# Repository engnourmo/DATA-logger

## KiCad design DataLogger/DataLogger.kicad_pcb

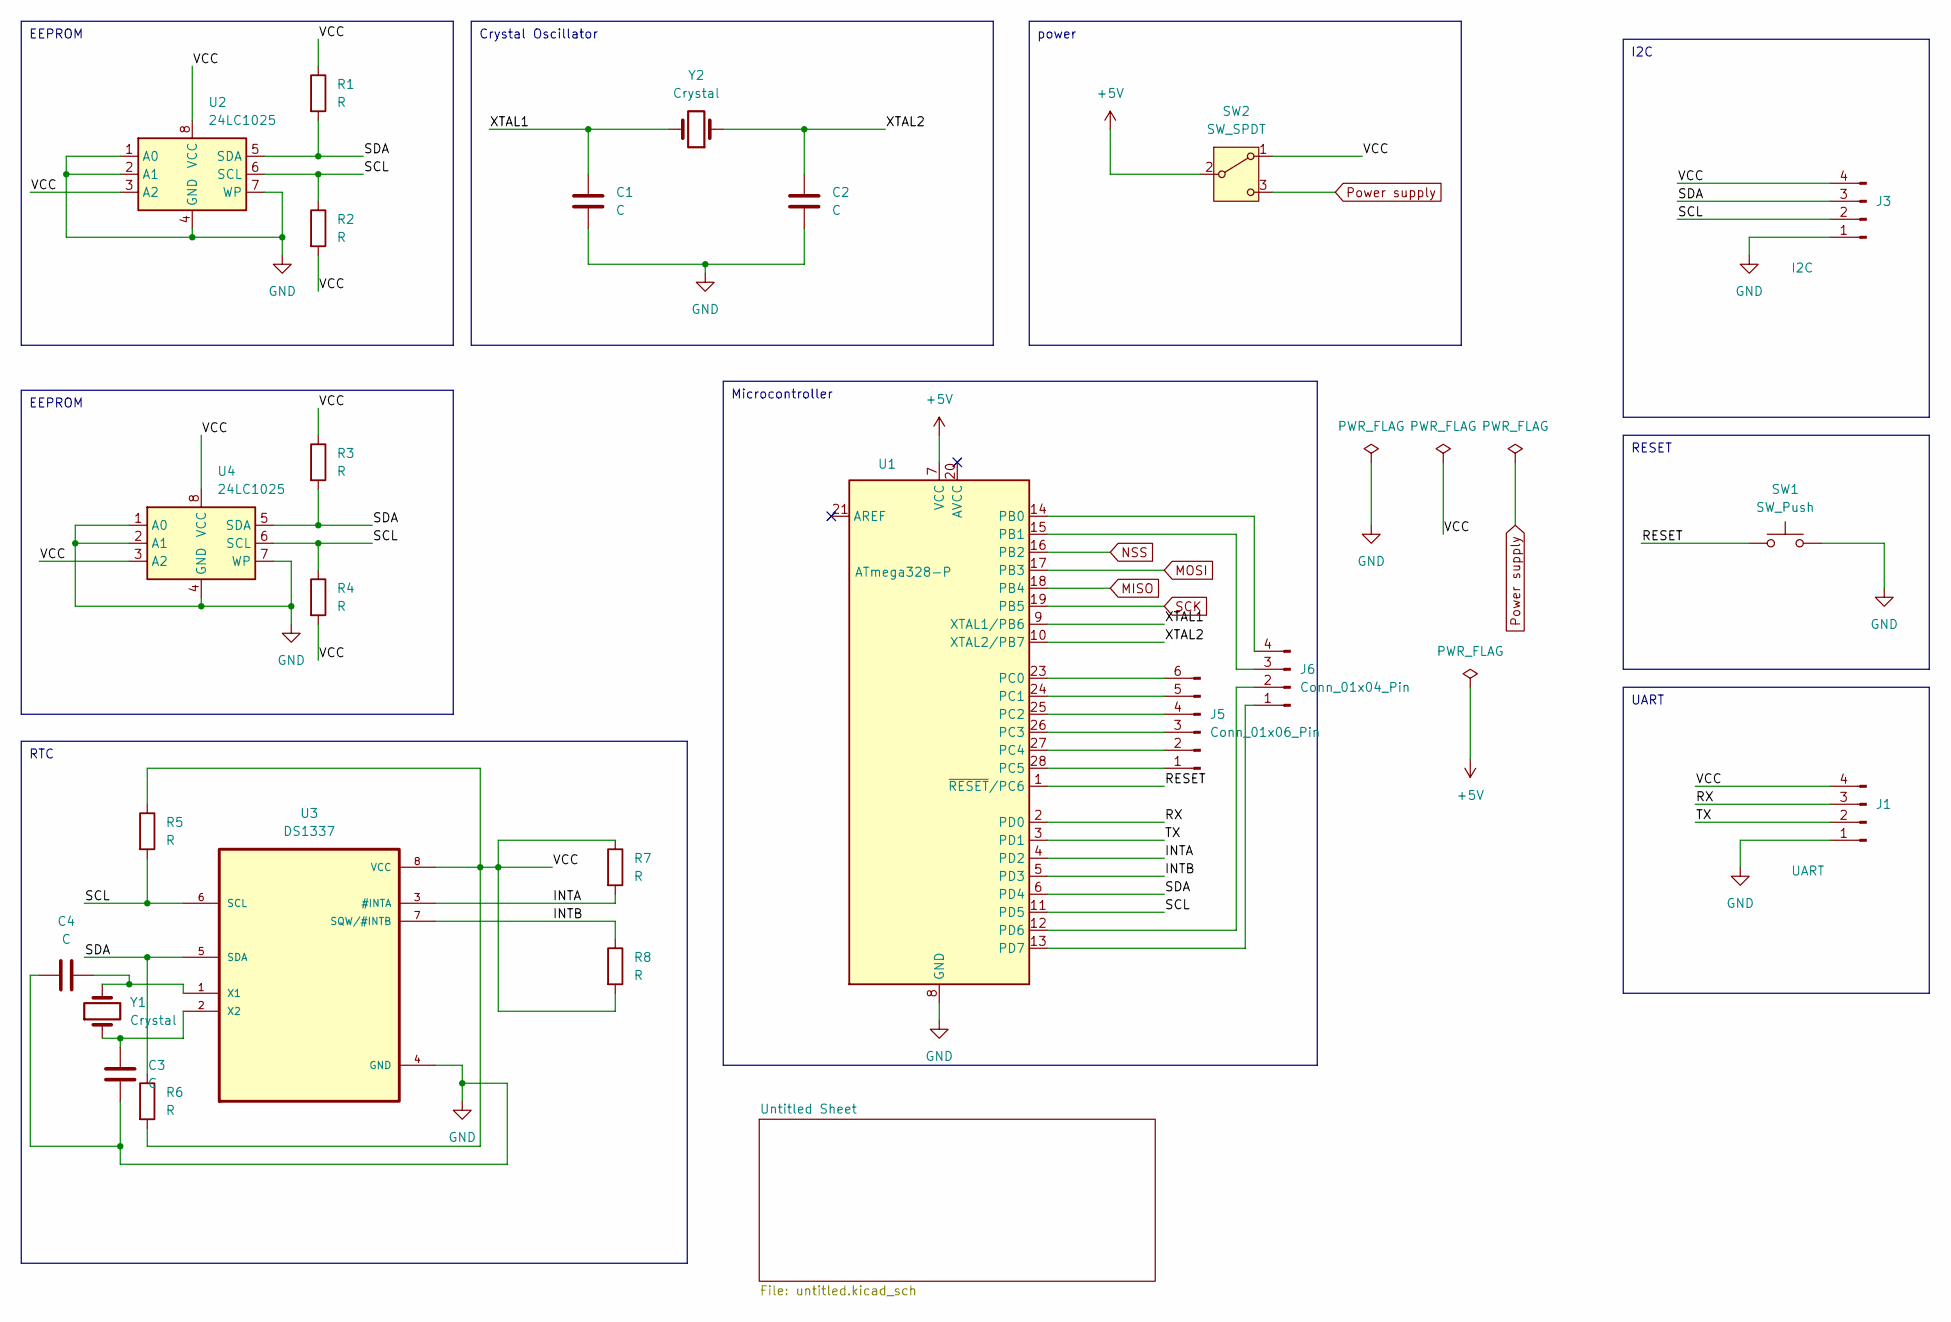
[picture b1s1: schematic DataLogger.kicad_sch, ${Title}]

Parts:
C1, C2, C3, C4: C; C_0402_1005Metric
J1: UART; Samtec_HPM-04-01-x-S_Straight_1x04_Pitch5.08mm
J3: I2C; Samtec_HPM-04-01-x-S_Straight_1x04_Pitch5.08mm
J5: Conn_01x06_Pin; Samtec_HPM-06-01-x-S_Straight_1x06_Pitch5.08mm
J6: Conn_01x04_Pin; Samtec_HPM-04-01-x-S_Straight_1x04_Pitch5.08mm
R1, R2, R3, R4, R5, R6, R7, R8: R; R_0603_1608Metric
SW1: SW_Push; SW_PUSH_6mm_H4.3mm
SW2: SW_SPDT; SW_MINI-SPDT-SW
U1: ATmega328-P; QFP80P900X900X120-32N
U2, U4: 24LC1025; SOIC-8_3.9x4.9mm_P1.27mm
U3: DS1337; DIP794W47P254L991H457Q8; DigiKey_Part_Number DS1337+-ND
Y1, Y2: Crystal; Crystal_HC49-4H_Vertical

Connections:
+5V: SW2.2 (B), U1.7 (VCC)
/INTA: R7.2, U1.4 (PD2), U3.3 (#INTA)
/INTB: R8.1, U1.5 (PD3), U3.7 (SQW/#INTB)
/RESET: SW1.1, U1.1 (~RESET/PC6)
/RX: J1.3, U1.2 (PD0)
/SCL: J3.2, R2.1, R4.1, R5.2, U1.11 (PD5), U2.6 (SCL), U3.6 (SCL), U4.6 (SCL)
/SDA: J3.3, R1.2, R3.2, R6.1, U1.6 (PD4), U2.5 (SDA), U3.5 (SDA), U4.5 (SDA)
/TX: J1.2, U1.3 (PD1)
/VCC: J1.4, J3.4, R1.1, R2.2, R3.1, R4.2, R5.1, R6.2, R7.1, R8.2, SW2.1 (A), U2.3 (A2), U2.8 (VCC), U3.8 (VCC), U4.3 (A2), U4.8 (VCC)
/XTAL1: C1.1, U1.9 (XTAL1/PB6), Y2.2
/XTAL2: C2.1, U1.10 (XTAL2/PB7), Y2.1
GND: C1.2, C2.2, C3.2, C4.1, J1.1, J3.1, SW1.2, U1.8 (GND), U1.22 (GND), U2.1 (A0), U2.2 (A1), U2.4 (GND), U2.7 (WP), U3.4 (GND), U4.1 (A0), U4.2 (A1), U4.4 (GND), U4.7 (WP); also elsewhere on the board
MISO: U1.18 (PB4); also elsewhere on the board
MOSI: U1.17 (PB3); also elsewhere on the board
NSS: U1.16 (PB2); also elsewhere on the board
unnamed: J5.1, U1.28 (PC5)
unnamed: J5.2, U1.27 (PC4)
unnamed: J5.3, U1.26 (PC3)
unnamed: J5.4, U1.25 (PC2)
unnamed: J5.5, U1.24 (PC1)
unnamed: J5.6, U1.23 (PC0)
unnamed: J6.1, U1.13 (PD7)
unnamed: J6.2, U1.12 (PD6)
unnamed: J6.3, U1.15 (PB1)
unnamed: J6.4, U1.14 (PB0)
unnamed: C4.2, U3.1 (X1), Y1.2
unnamed: C3.1, U3.2 (X2), Y1.1
Power supply: SW2.3 (C); also elsewhere on the board
SCK: U1.19 (PB5); also elsewhere on the board

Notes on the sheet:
UART
Microcontroller
power
Crystal Oscillator
EEPROM
I2C
RTC
RESET

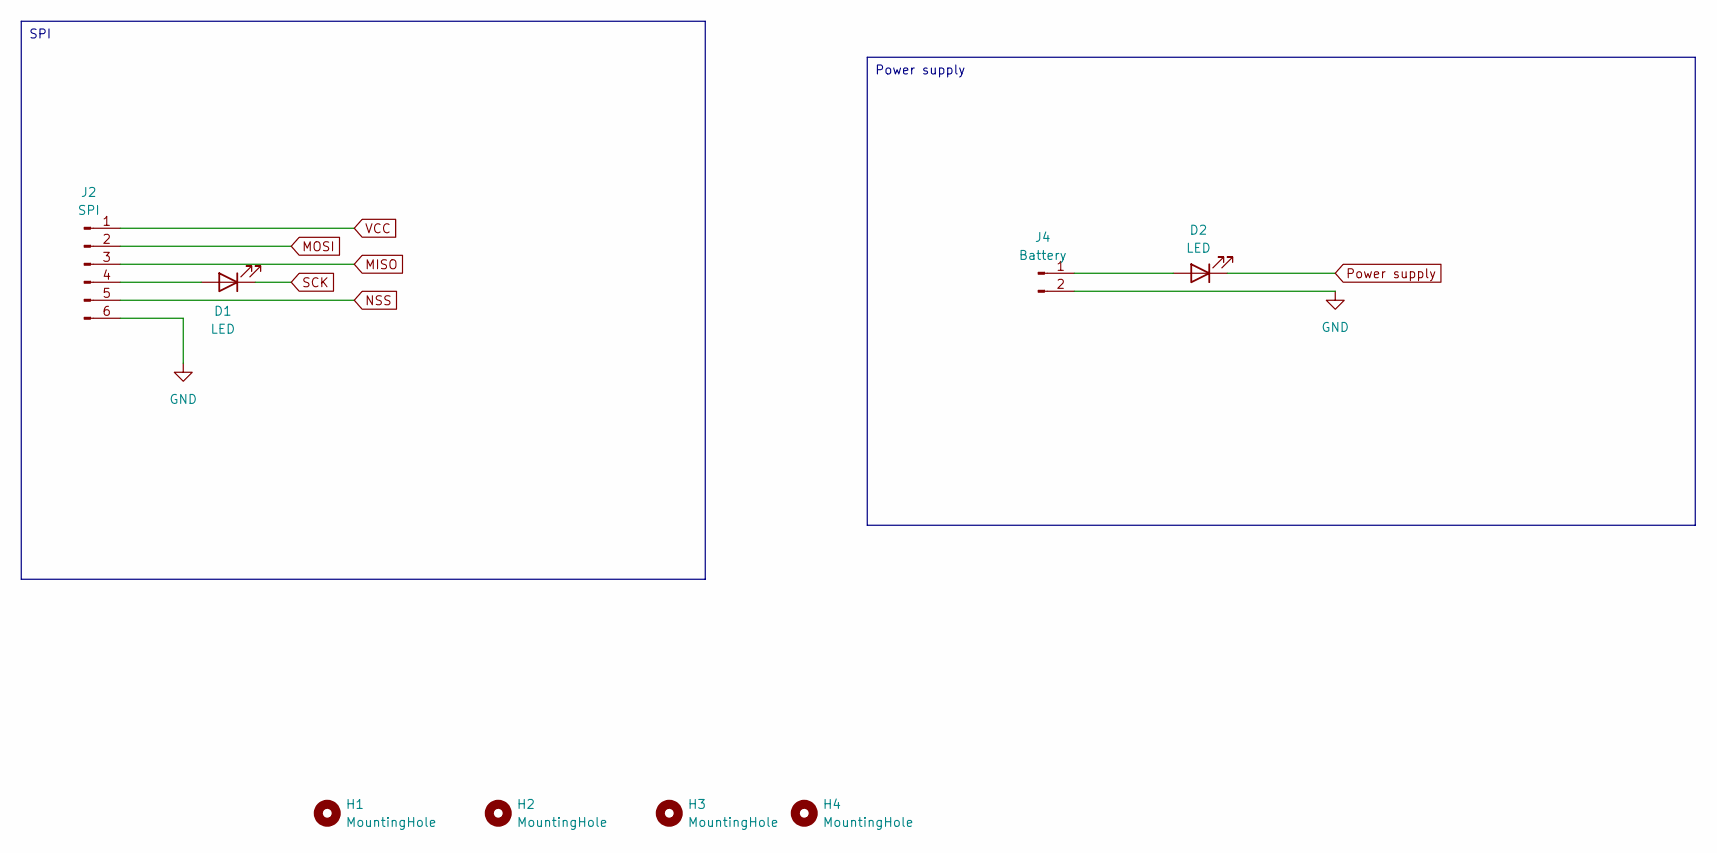
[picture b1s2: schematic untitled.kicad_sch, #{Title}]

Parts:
D1, D2: LED; LED_0603_1608Metric
H1, H2, H3, H4: MountingHole; MountingHole_2.2mm_M2_DIN965_Pad
J2: SPI; Samtec_HPM-06-01-x-S_Straight_1x06_Pitch5.08mm
J4: Battery; Samtec_HPM-02-01-x-S_Straight_1x02_Pitch5.08mm

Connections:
GND: J2.6, J4.2; also elsewhere on the board
MISO: J2.3; also elsewhere on the board
MOSI: J2.2; also elsewhere on the board
NSS: J2.5; also elsewhere on the board
unnamed: D1.2 (A), J2.4
unnamed: D2.2 (A), J4.1
Power supply: D2.1 (K); also elsewhere on the board
SCK: D1.1 (K); also elsewhere on the board
VCC: J2.1

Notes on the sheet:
SPI
Power supply

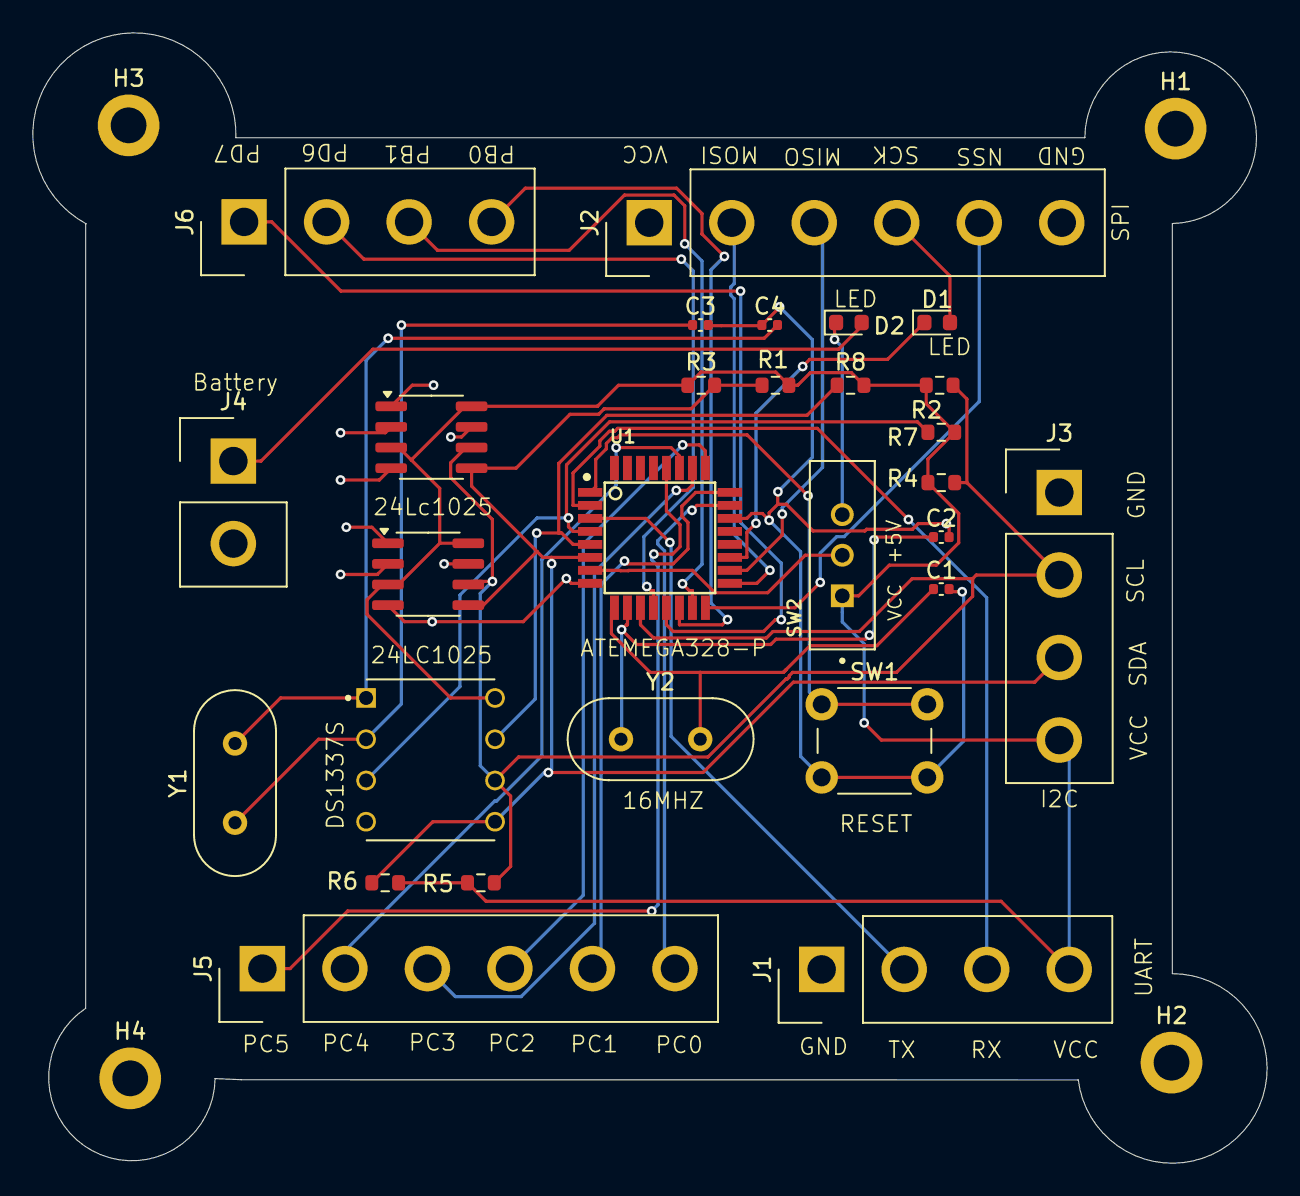
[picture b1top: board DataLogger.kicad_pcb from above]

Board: 2 copper layers, 76.0 x 69.6 mm, 32 parts (0 on the bottom side), 31 nets.

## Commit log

2025-03-27 added project files
2025-03-27 added ATMEGA symbol
2025-03-27 modified some tracks
2025-04-18 edited new tracks
2025-04-18 readded files of pcb
2025-04-18 add BOMs and gerber files
2025-04-18 edit layer of measurment
2025-04-18 edit via
